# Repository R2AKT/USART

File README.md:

License addendum - https://github.com/R2AKT/USART/blob/main/Addendum.txt
# USART

Serial port module (USART). For Mega-80 (Mega-580) DIY 8-bit micro-computer - https://github.com/R2AKT/Mega-80.

Based on 580VV51 (8251) and 580VI53 (8253).

Status: Tested. Prescaler x1 and x16, speed up to 38400.

Модуль последовательного порта (USART). Для самодельной 8-битной микро-ЭВМ - https://github.com/R2AKT/Mega-80.

На основе 580ВВ51 (8251) и 580ВИ53 (8253).

Статус: Протестирован. Работает в режиме x1 и x16, на скорости до 38400.

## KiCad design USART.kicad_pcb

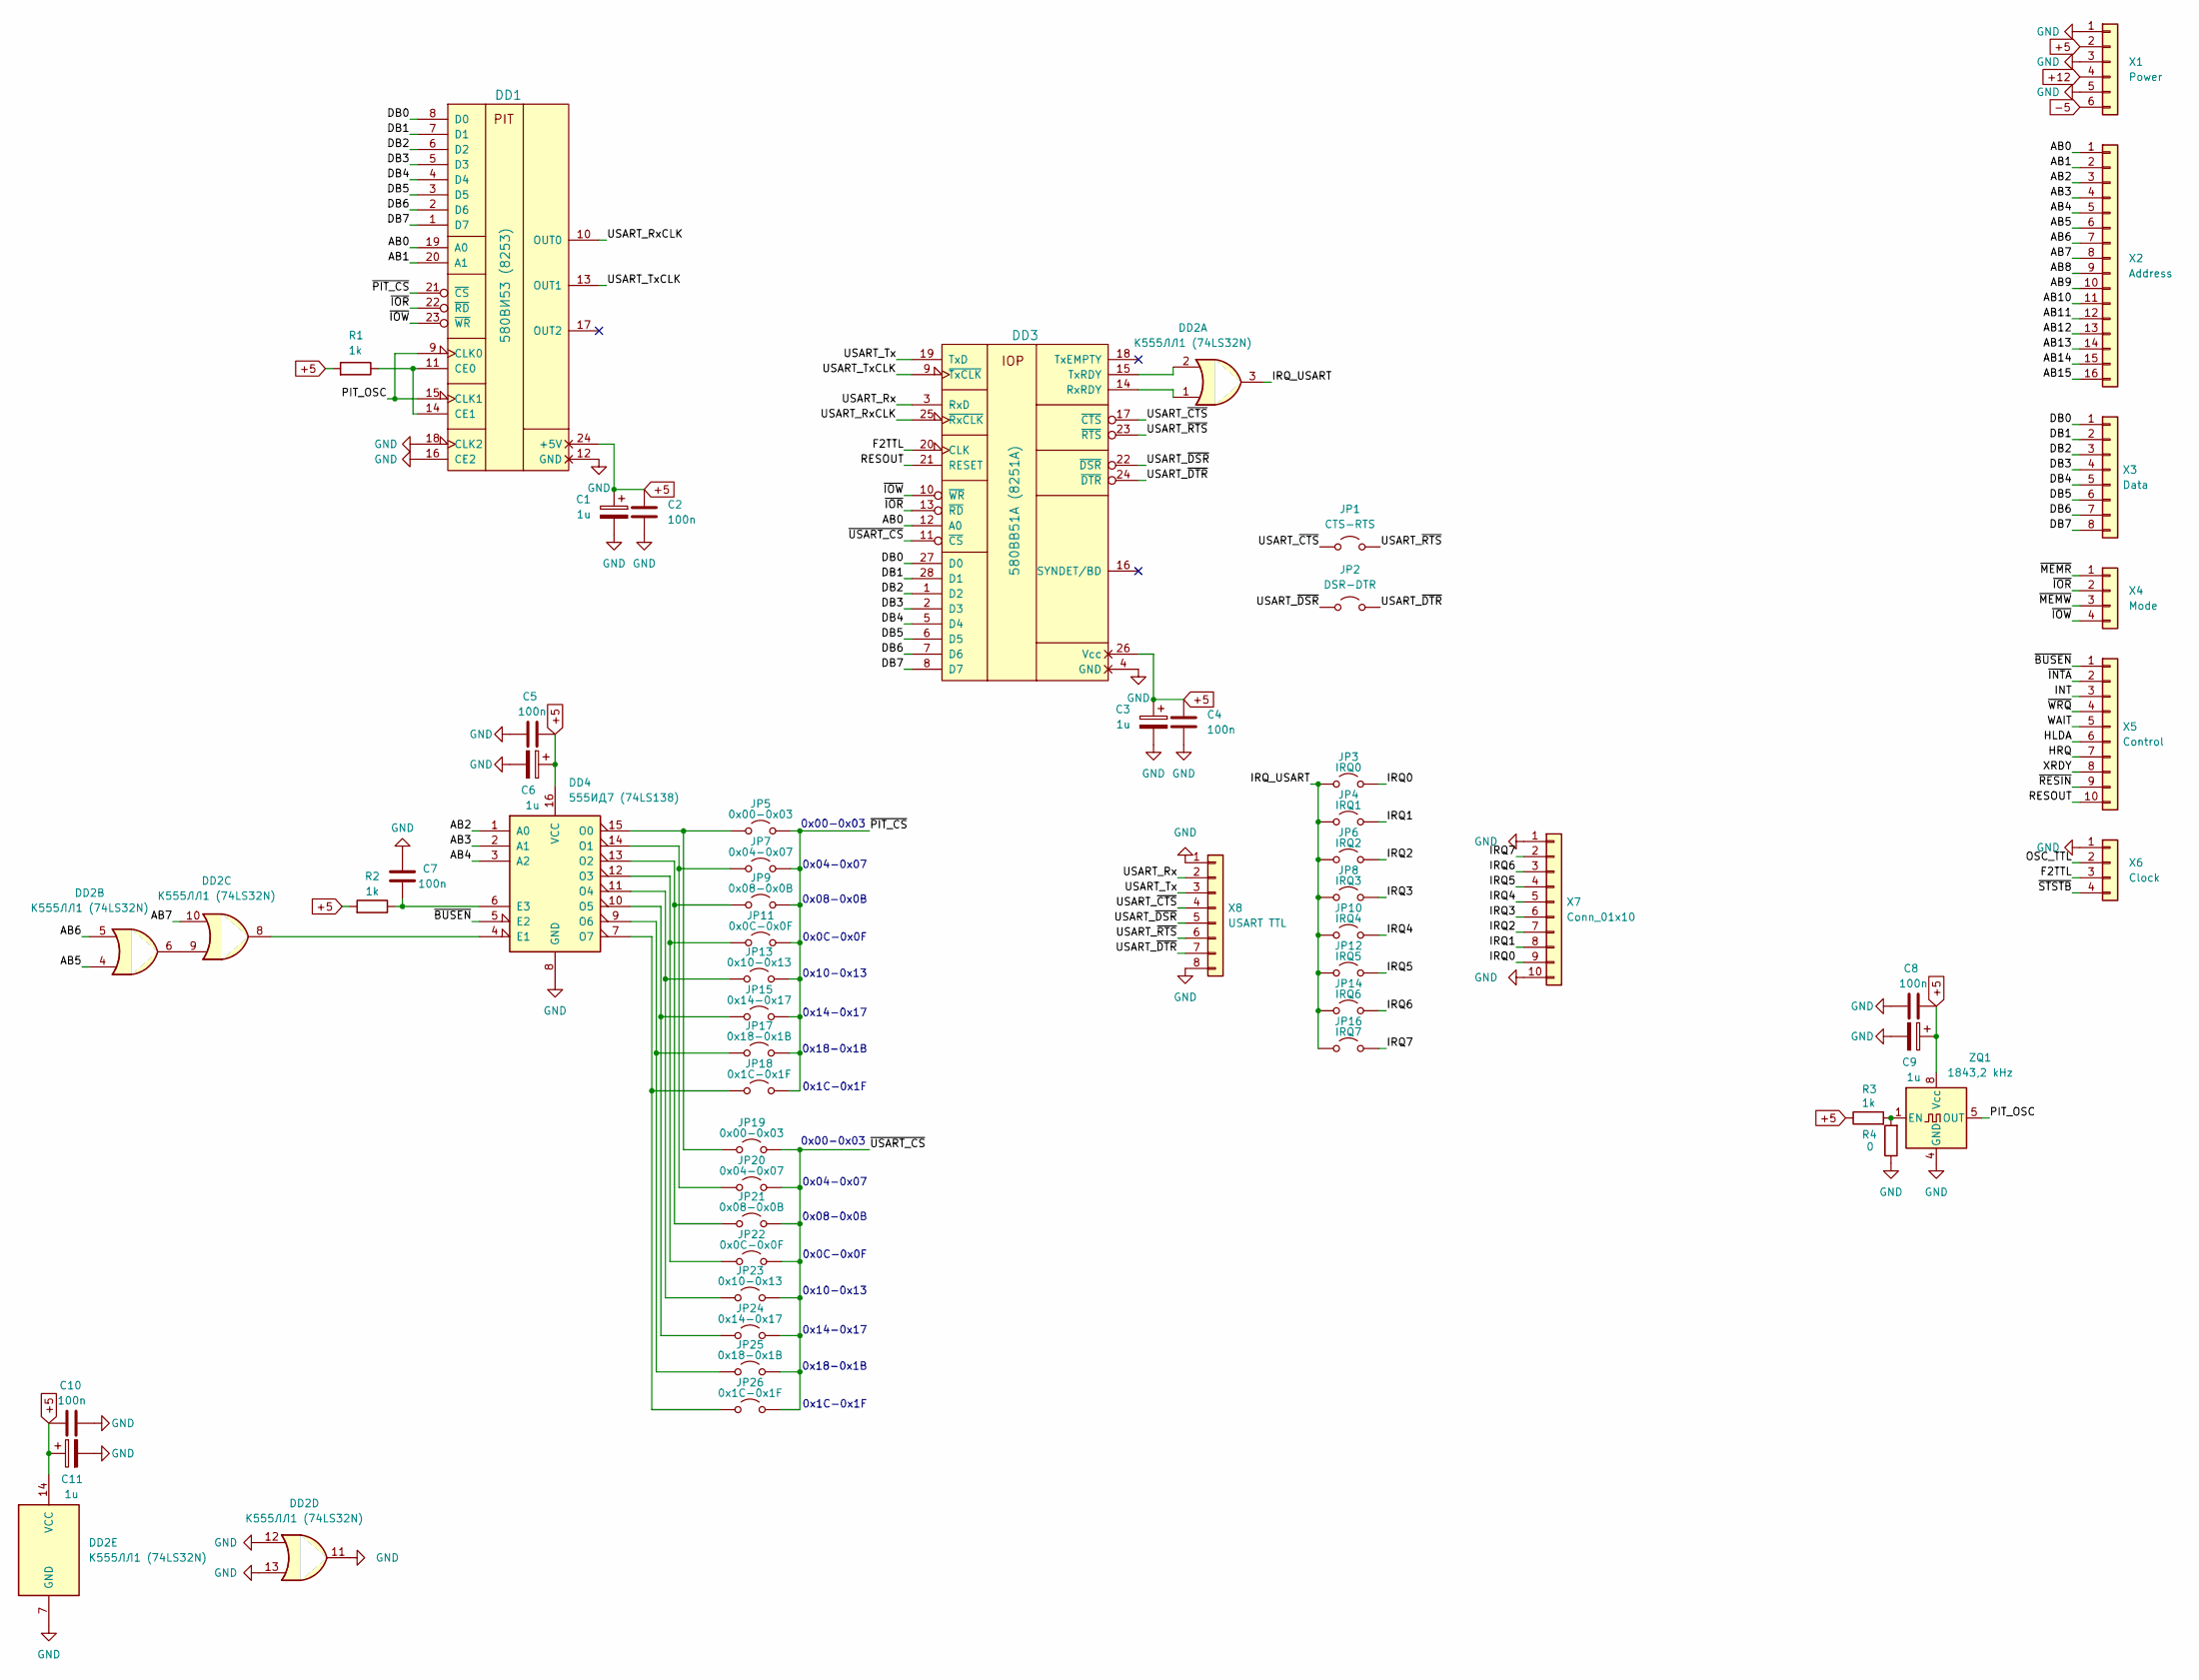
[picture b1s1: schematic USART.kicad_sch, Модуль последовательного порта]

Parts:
C1, C3, C6, C9, C11: 1u; CP_EIA-3216-18_Kemet-A_Pad1.58x1.35mm_HandSolder
C2, C4, C5, C7, C8, C10: 100n; C_0805_2012Metric_Pad1.18x1.45mm_HandSolder
DD1: 580ВИ53 (8253); DIP-24_W15.24mm_Socket_LongPads
DD2: К555ЛЛ1 (74LS32N); DIP-14_W7.62mm_Socket_LongPads
DD3: 580ВВ51А (8251A); DIP-28_W15.24mm_Socket_LongPads
DD4: 555ИД7 (74LS138); DIP-16_W7.62mm_Socket_LongPads
JP1: CTS-RTS; PinHeader_1x02_P2.54mm_Vertical
JP2: DSR-DTR; PinHeader_1x02_P2.54mm_Vertical
JP3: IRQ0; SolderJumper-2_P1.3mm_Open_RoundedPad1.0x1.5mm
JP4: IRQ1; SolderJumper-2_P1.3mm_Open_RoundedPad1.0x1.5mm
JP5, JP19: 0x00-0x03; SolderJumper-2_P1.3mm_Open_RoundedPad1.0x1.5mm
JP6: IRQ2; SolderJumper-2_P1.3mm_Open_RoundedPad1.0x1.5mm
JP7, JP20: 0x04-0x07; SolderJumper-2_P1.3mm_Open_RoundedPad1.0x1.5mm
JP8: IRQ3; SolderJumper-2_P1.3mm_Open_RoundedPad1.0x1.5mm
JP9, JP21: 0x08-0x0B; SolderJumper-2_P1.3mm_Open_RoundedPad1.0x1.5mm
JP10: IRQ4; SolderJumper-2_P1.3mm_Open_RoundedPad1.0x1.5mm
JP11, JP22: 0x0C-0x0F; SolderJumper-2_P1.3mm_Open_RoundedPad1.0x1.5mm
JP12: IRQ5; SolderJumper-2_P1.3mm_Open_RoundedPad1.0x1.5mm
JP13, JP23: 0x10-0x13; SolderJumper-2_P1.3mm_Open_RoundedPad1.0x1.5mm
JP14: IRQ6; SolderJumper-2_P1.3mm_Open_RoundedPad1.0x1.5mm
JP15, JP24: 0x14-0x17; SolderJumper-2_P1.3mm_Open_RoundedPad1.0x1.5mm
JP16: IRQ7; SolderJumper-2_P1.3mm_Open_RoundedPad1.0x1.5mm
JP17, JP25: 0x18-0x1B; SolderJumper-2_P1.3mm_Open_RoundedPad1.0x1.5mm
JP18, JP26: 0x1C-0x1F; SolderJumper-2_P1.3mm_Open_RoundedPad1.0x1.5mm
R1, R2, R3: 1k; R_0805_2012Metric_Pad1.20x1.40mm_HandSolder
R4: 0; R_0805_2012Metric_Pad1.20x1.40mm_HandSolder
X1: Power; PinHeader_1x06_P2.54mm_Vertical
X2: Address; PinHeader_1x16_P2.54mm_Vertical
X3: Data; PinHeader_1x08_P2.54mm_Vertical
X4: Mode; PinHeader_1x04_P2.54mm_Vertical
X5: Control; PinHeader_1x10_P2.54mm_Vertical
X6: Clock; PinHeader_1x04_P2.54mm_Vertical
X7: Conn_01x10; PinHeader_1x10_P2.54mm_Vertical
X8: USART TTL; PinHeader_1x08_P2.54mm_Horizontal
ZQ1: 1843,2 kHz; Oscillator_DIP-8_LargePads

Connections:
+5: C1.1, C2.1, C3.1, C4.1, C5.1, C6.1, C8.1, C9.1, C10.1, C11.1, DD1.24 (+5V), DD2.14 (VCC), DD3.26 (Vcc), DD4.16 (VCC), R1.2, R2.2, R3.1, X1.2, ZQ1.8 (Vcc)
+12: X1.4
-5: X1.6
/AB0: DD1.19 (A0), DD3.12 (A0), X2.1
/AB1: DD1.20 (A1), X2.2
/AB2: DD4.1 (A0), X2.3
/AB3: DD4.2 (A1), X2.4
/AB4: DD4.3 (A2), X2.5
/AB5: DD2.4, X2.6
/AB6: DD2.5, X2.7
/AB7: DD2.10, X2.8
/AB8: X2.9
/AB9: X2.10
/AB10: X2.11
/AB11: X2.12
/AB12: X2.13
/AB13: X2.14
/AB14: X2.15
/AB15: X2.16
/DB0: DD1.8 (D0), DD3.27 (D0), X3.1
/DB1: DD1.7 (D1), DD3.28 (D1), X3.2
/DB2: DD1.6 (D2), DD3.1 (D2), X3.3
/DB3: DD1.5 (D3), DD3.2 (D3), X3.4
/DB4: DD1.4 (D4), DD3.5 (D4), X3.5
/DB5: DD1.3 (D5), DD3.6 (D5), X3.6
/DB6: DD1.2 (D6), DD3.7 (D6), X3.7
/DB7: DD1.1 (D7), DD3.8 (D7), X3.8
/F2TTL: DD3.20 (CLK), X6.3
/HLDA: X5.6
/HRQ: X5.7
/INT: X5.3
/IRQ0: JP3.2 (B), X7.9
/IRQ1: JP4.2 (B), X7.8
/IRQ2: JP6.2 (B), X7.7
/IRQ3: JP8.2 (B), X7.6
/IRQ4: JP10.2 (B), X7.5
/IRQ5: JP12.2 (B), X7.4
/IRQ6: JP14.2 (B), X7.3
/IRQ7: JP16.2 (B), X7.2
/IRQ_USART: DD2.3, JP3.1 (A), JP4.1 (A), JP6.1 (A), JP8.1 (A), JP10.1 (A), JP12.1 (A), JP14.1 (A), JP16.1 (A)
/OSC_TTL: X6.2
/PIT_OSC: DD1.9 (CLK0), DD1.15 (CLK1), ZQ1.5 (OUT)
/RESOUT: DD3.21 (RESET), X5.10
/USART_Rx: DD3.3 (RxD), X8.2
/USART_RxCLK: DD1.10 (OUT0), DD3.25 (~RxCLK)
/USART_Tx: DD3.19 (TxD), X8.3
/USART_TxCLK: DD1.13 (OUT1), DD3.9 (~TxCLK)
/USART_~CTS: DD3.17 (~CTS), JP1.1 (A), X8.4
/USART_~DSR: DD3.22 (~DSR), JP2.1 (A), X8.5
/USART_~DTR: DD3.24 (~DTR), JP2.2 (B), X8.7
/USART_~RTS: DD3.23 (~RTS), JP1.2 (B), X8.6
/WAIT: X5.5
/XRDY: X5.8
/~BUSEN: DD4.5 (E2), X5.1
/~INTA: X5.2
/~IOR: DD1.22 (~RD), DD3.13 (~RD), X4.2
/~IOW: DD1.23 (~WR), DD3.10 (~WR), X4.4
/~MEMR: X4.1
/~MEMW: X4.3
/~PIT_CS: DD1.21 (~CS), JP5.2 (B), JP7.2 (B), JP9.2 (B), JP11.2 (B), JP13.2 (B), JP15.2 (B), JP17.2 (B), JP18.2 (B)
/~RESIN: X5.9
/~STSTB: X6.4
/~USART_CS: DD3.11 (~CS), JP19.2 (B), JP20.2 (B), JP21.2 (B), JP22.2 (B), JP23.2 (B), JP24.2 (B), JP25.2 (B), JP26.2 (B)
/~WRQ: X5.4
GND: C1.2, C2.2, C3.2, C4.2, C5.2, C6.2, C7.2, C8.2, C9.2, C10.2, C11.2, DD1.12 (GND), DD1.16 (CE2), DD1.18 (CLK2), DD2.7 (GND), DD2.11, DD2.12, DD2.13, DD3.4 (GND), DD4.8 (GND), R4.1, X1.1, X1.3, X1.5, X6.1, X7.1, X7.10, X8.1, X8.8, ZQ1.4 (GND)
unnamed: DD1.11 (CE0), DD1.14 (CE1), R1.1
unnamed: DD2.6, DD2.9
unnamed: DD2.1, DD3.14 (RxRDY)
unnamed: DD2.2, DD3.15 (TxRDY)
unnamed: DD2.8, DD4.4 (E1)
unnamed: C7.1, DD4.6 (E3), R2.1
unnamed: DD4.15 (O0), JP5.1 (A), JP19.1 (A)
unnamed: DD4.14 (O1), JP7.1 (A), JP20.1 (A)
unnamed: DD4.13 (O2), JP9.1 (A), JP21.1 (A)
unnamed: DD4.12 (O3), JP11.1 (A), JP22.1 (A)
unnamed: DD4.11 (O4), JP13.1 (A), JP23.1 (A)
unnamed: DD4.10 (O5), JP15.1 (A), JP24.1 (A)
unnamed: DD4.9 (O6), JP17.1 (A), JP25.1 (A)
unnamed: DD4.7 (O7), JP18.1 (A), JP26.1 (A)
unnamed: R3.2, R4.2, ZQ1.1 (EN)

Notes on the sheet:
0x00-0x03
0x1C-0x1F
0x18-0x1B
0x08-0x0B
0x14-0x17
0x10-0x13
0x04-0x07
0x0C-0x0F

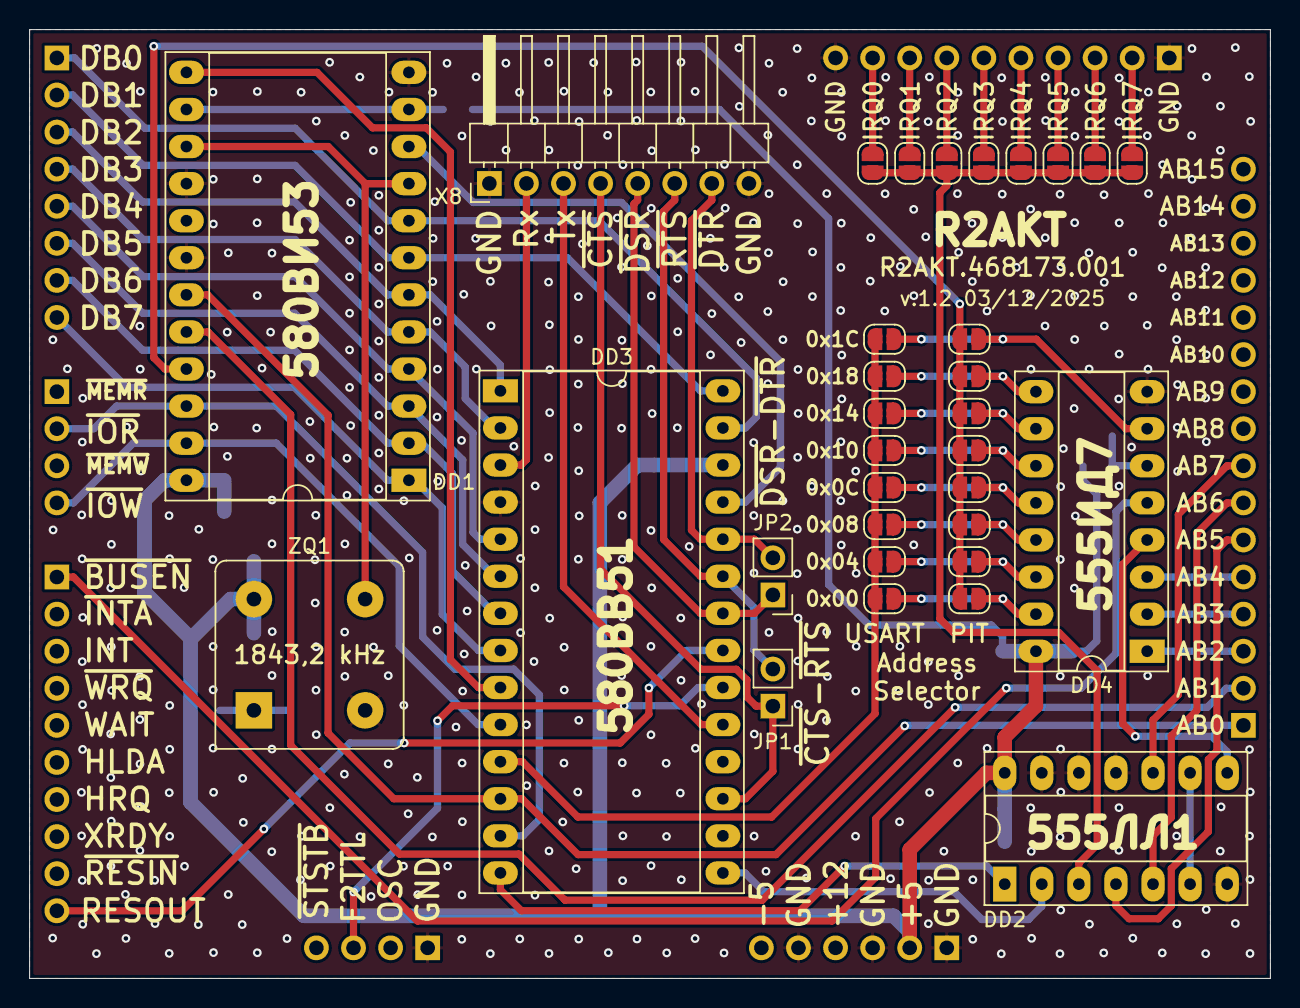
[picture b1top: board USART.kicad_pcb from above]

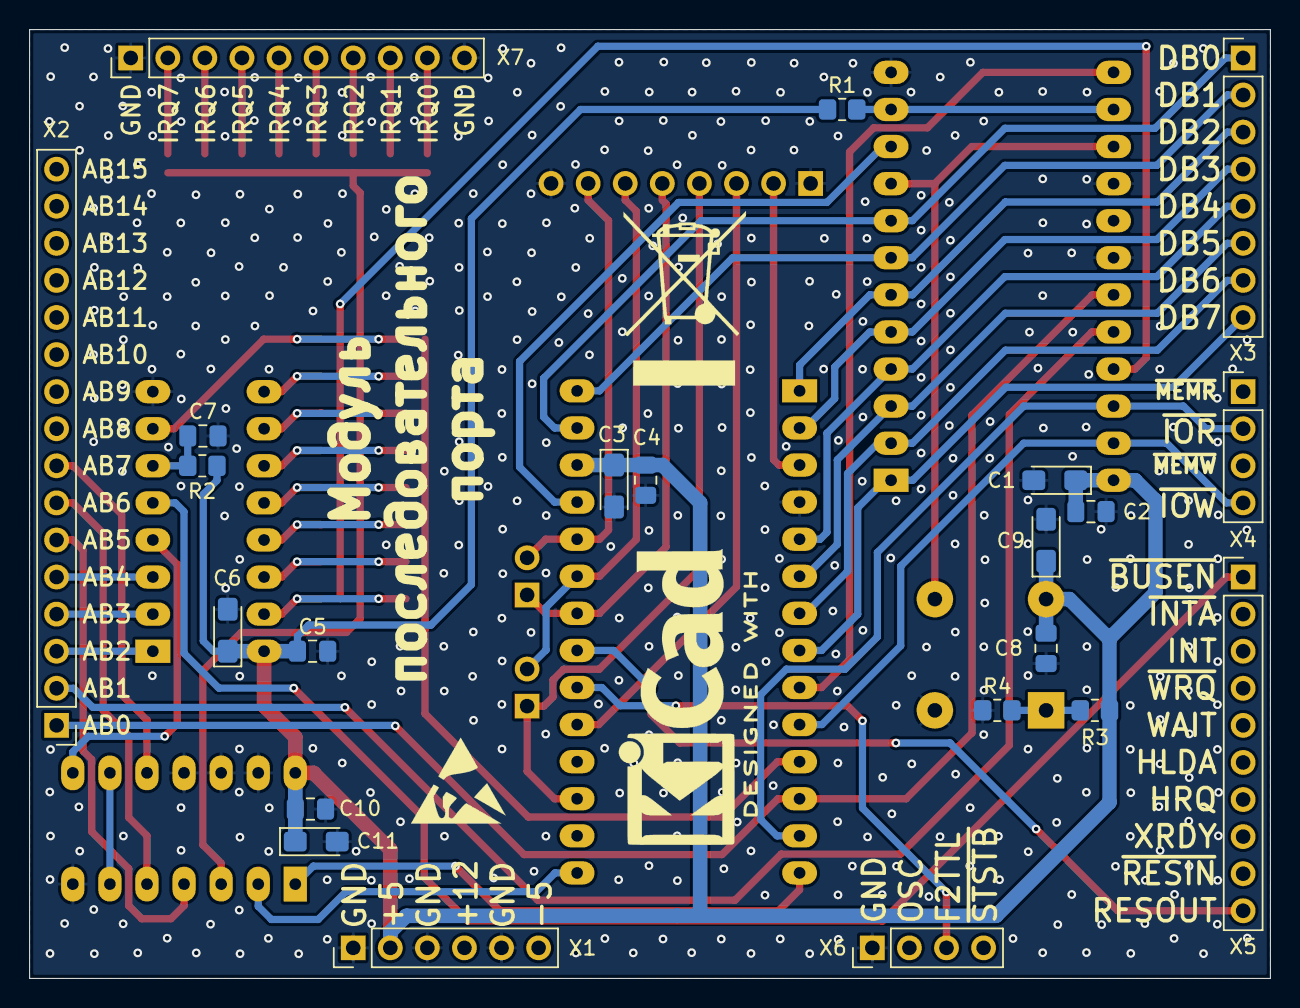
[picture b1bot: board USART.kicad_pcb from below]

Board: 2 copper layers, 85.0 x 65.0 mm, 54 parts (22 on the bottom side), 58 nets.

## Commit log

2025-12-03 Update+fix
    - Replaced the standard logic oscillator with a monolithic quartz oscillator;
    - Fixed the 'CLK' source of the 580VV51 (8251);
    - Connected the reset signal of the 580VV51 (8251).
    - Заменен генератор на стандартной логике на монолитный кварцевый генератор;
    - Исправлен источник 'CLK' у 580ВВ51 (8251);
    - Подключен сигнал сброса у 580ВВ51 (8251).
2025-12-04 Add files via upload
    Added a table of speed generator frequencies and divider values for different exchange rates.
    Добавлена таблица частот генератора скорости и значения делителя для различных скоростей обмена.
2026-01-20 Add files via upload
    Changed IRQ bus pin's
    Изменены пины шины IRQ
2026-03-08 Add files via upload
    Software implementation. Base function's.
    Программная реализация. Базовые функции.

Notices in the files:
README.md:
License: MIT
